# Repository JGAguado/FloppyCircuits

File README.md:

[![GitHub Release][releases-shield]][releases]
[![License][license-shield]](LICENSE)

[![Project Maintenance][maintenance-shield]][maintenance]
[![BuyMeCoffee][buymecoffee-shield]][buymecoffee]

# Floppy Circuits

## Index of circuits:

* Module green: Basics
  * Project I: Ohm's Law (Potentiometer with LED)
  * Project II: Resistors (Parallel vs Series)
  * Project III: Capacitors (Charge and discharge of a capacitor with a led)
  * Project IV: Inductors (Inductor kickback circuit)
  * Project V: Transistors (Light sensor)
* Module yellow: Power
  * Project I: Wireless charger
  * Project II: Rectification stage
  * Project III: Linear regulation
  * Project IV: Step down converter
  * Project V: Step up converter
* Module red: Amplifiers
  * Project I: Inverting op-amp
  * Project II: Non-inverting op-amp
  * Project III: Voltage adder
  * Project IV: Voltage substractor
  * Project V: Voltage comparator
* Module blue: Digital systems
  * Project I: Logic Gates
  * Project II: Flip Flops
  * Project III: BCD to 7s decoder
  * Project IV: Decade Counter
  * Project V: Relay circuit
* Module white: Signal generator
  * Project I: Astable multivibrator
  * Project II: 555 Timer monostable
  * Project III: 555 Timer astable
  * Project IV: Triangular signal from square
  * Project V: Wien Bridge oscillator
* Module black: Filters
  * Project I: Low-pass 
  * Project II: High-pass
  * Project III: Band-pass filter
  * Project IV: Stop-band filter
  * Project V: Butterworth low-pass filter

## Repository Contents
-------------------
* **/01_Documentation** - Data sheets, schematics, illustrations (.pdf)
* **/02_Hardware** - All Eagle design files (.brd, .sch)
* **/03_Software** - MCU code files (.ino, .py, .cpp)
* **/04_Production** - All manufacturing files (BOM, centroids, Gerbers)

[releases-shield]: https://img.shields.io/github/release/JGAguado/FloppyCircutis.svg?style=for-the-badge
[releases]: https://github.com/JGAguado/Fuel_Tracker/releases

[license-shield]: https://img.shields.io/github/license/JGAguado/FloppyCircuits.svg?style=for-the-badge

[maintenance-shield]: https://img.shields.io/badge/maintainer-J.%20G.%20Aguado-blue.svg?style=for-the-badge
[maintenance]: https://github.com/JGAguado

[buymecoffee-shield]: https://img.shields.io/badge/buy%20me%20a%20coffee-support-yellow.svg?style=for-the-badge
[buymecoffee]: https://www.buymeacoffee.com/J.G.Aguado

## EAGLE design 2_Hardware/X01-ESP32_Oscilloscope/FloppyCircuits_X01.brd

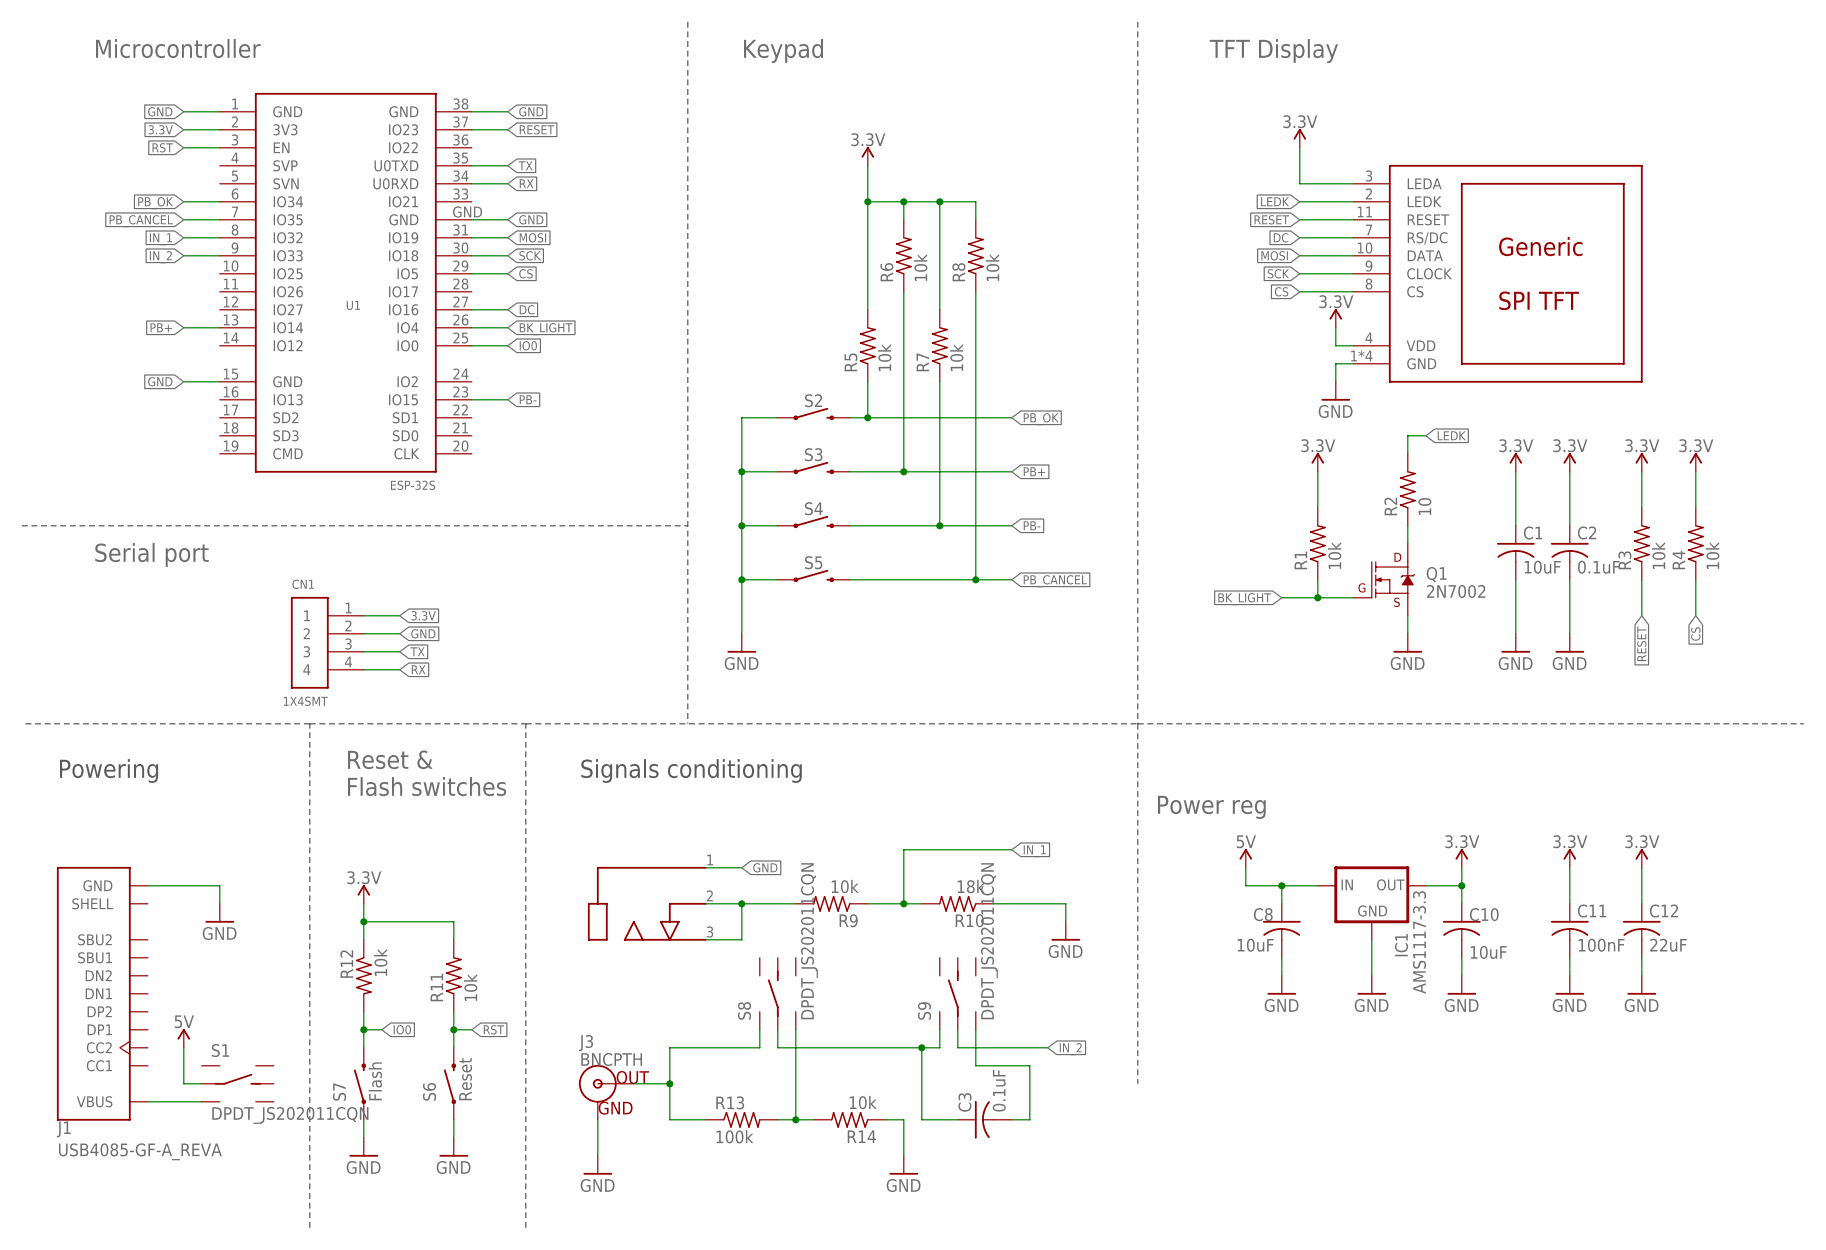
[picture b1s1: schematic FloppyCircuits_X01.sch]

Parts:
C1, C8, C10: 10uF; C0603
C2, C3: 0.1uF; C0603
C11: 100nF; C0603
C12: 22uF; C0603
CN1: 1X4SMT; 1X4-SMT
DISP1: DISP_LCD_GENERIC_SPI_1.69_WRAPUNDER; TFT_1.69IN_240X280_12P
IC1: AMS1117-3.3; SOT223
J1: USB4085-GF-A_REVA; GCT_USB4085-GF-A_REVA
J2: AUDIO_JACK_MONO_3.5; PJ316_3.5
J3: BNCPTH; BNC
Q1: 2N7002; SOT23-3
R1, R3, R4, R5, R6, R7, R8, R9, R11, R12, R14: 10k; R0603
R2: 10; R0603
R10: 18k; R0603
R13: 100k; R0603
S1, S8, S9: DPDT_JS202011CQN
S2, S3, S4, S5: MOMENTARY-SWITCH-SPST-PTH-6.0MM; TACTILE_SWITCH_PTH_6.0MM
S6: Reset; TACTILE_SWITCH_SMD_5.2MM
S7: Flash; TACTILE_SWITCH_SMD_5.2MM
U1: ESP-32S

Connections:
3.3V: C1.1, C2.1, C10.1, C11.1, C12.1, CN1.1, DISP1.3 (LEDA), DISP1.4 (VDD), IC1.2 (OUT), R1.2, R3.2, R4.2, R5.2, R6.2, R7.2, R8.2, R11.2, R12.1, U1.2 (3V3)
5V: C8.1, IC1.3 (IN), S1.2 (LC)
BK_LIGHT: Q1.1 (G), R1.1, U1.26 (IO4)
CS: DISP1.8 (CS), R4.1, U1.29 (IO5)
DC: DISP1.7 (RS/DC), U1.27 (IO16)
GND: C1.2, C2.2, C8.2, C10.2, C11.2, C12.2, CN1.2, DISP1.1 (GND), DISP1.5 (GND), DISP1.6 (GND), DISP1.12 (GND), IC1.1 (GND), J1.A1 (GND), J1.A12 (GND), J1.B1 (GND), J1.B12 (GND), J2.1, J3.GND, Q1.2 (S), R10.1, R14.1, S2.1, S3.1, S4.1, S5.1, S6.1, S7.1, U1.1 (GND), U1.15 (GND), U1.38 (GND), U1.GND
INPUT: J2.2, J2.3, R9.2
IN_1: R9.1, R10.2, U1.8 (IO32)
IN_2: S9.2 (LC), U1.9 (IO33)
IO0: R12.2, S7.3 (2), U1.25 (IO0)
LEDK: DISP1.2 (LEDK), R2.2
MOSI: DISP1.10 (DATA), U1.31 (IO19)
unnamed: Q1.3 (D), R2.1
unnamed: J3.S (OUT), R13.1, S8.1 (L1)
unnamed: R13.2, R14.2, S8.3 (L2)
unnamed: J1.A4 (VBUS), J1.A9 (VBUS), J1.B4 (VBUS), J1.B9 (VBUS), S1.3 (L2)
unnamed: C3.1, S8.2 (LC), S9.1 (L1)
unnamed: C3.2, S9.3 (L2)
PB+: R6.1, S3.3 (2), U1.13 (IO14)
PB-: R7.1, S4.3 (2), U1.23 (IO15)
PB_CANCEL: R8.1, S5.3 (2), U1.7 (IO35)
PB_OK: R5.1, S2.3 (2), U1.6 (IO34)
RESET: DISP1.11 (RESET), R3.1, U1.37 (IO23)
RST: R11.1, S6.3 (2), U1.3 (EN)
RX: CN1.4, U1.34 (U0RXD)
SCK: DISP1.9 (CLOCK), U1.30 (IO18)
TX: CN1.3, U1.35 (U0TXD)

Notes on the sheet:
Powering
Signals conditioning
Microcontroller
TFT Display
Power reg
Keypad
Reset & Flash switches
Serial port

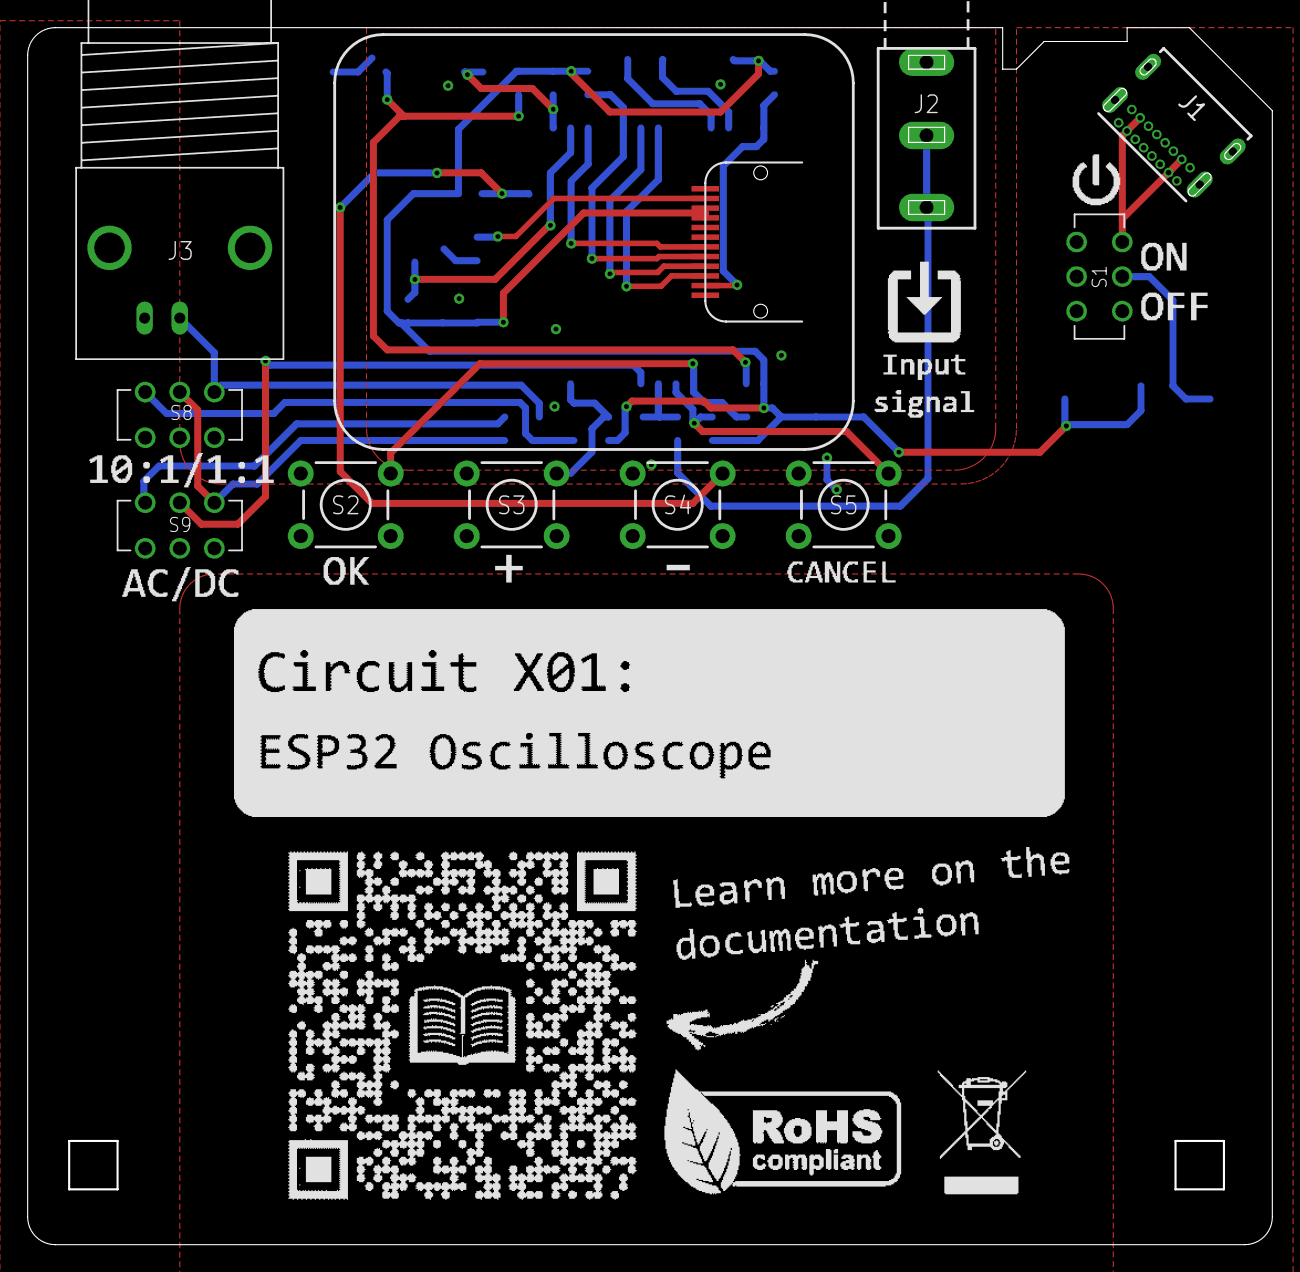
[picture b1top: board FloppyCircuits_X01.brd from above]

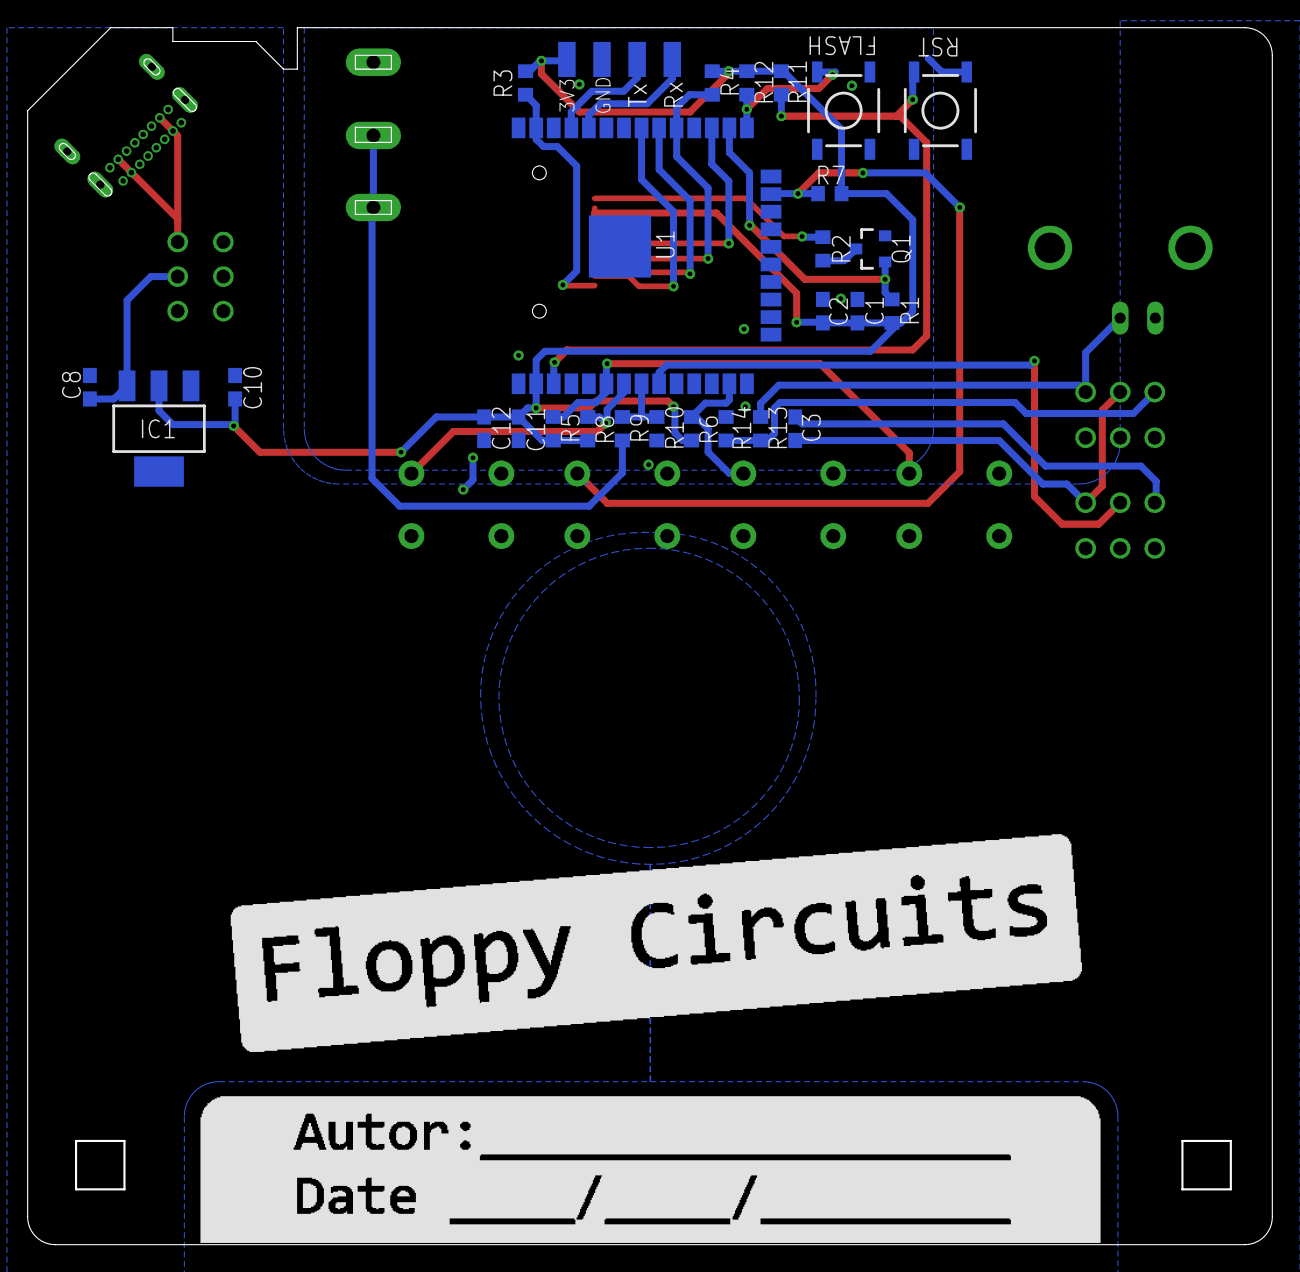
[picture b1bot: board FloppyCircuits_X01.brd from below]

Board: 2 copper layers, 90.0 x 88.0 mm, 38 parts (27 on the bottom side), 27 nets.

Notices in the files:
parts and their libraries:
SparkFun-PowerSymbols: Licensing: Creative Commons ShareAlike 4.0 International - https://creativecommons.org/licenses/by-sa/4.0
esp32: Creative Commons Attribution-ShareAlike 4.0 International
